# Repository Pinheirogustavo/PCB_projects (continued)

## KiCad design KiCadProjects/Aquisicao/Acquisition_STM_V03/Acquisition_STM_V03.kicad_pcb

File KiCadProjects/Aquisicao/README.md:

# Placa de Aquisição 

## Versão atual em produção (jlcpcb:): 01

## Descrição Geral do projeto
 As placas de aquisição tem a função de suportar os módulos de microcontroladores stm32 modelo bluepill, empregados na demodulação de sinais.

### Versão 01

Esta versão suporta até 4 módulos stm32 bluepill. Onde é possível demodular 4 ou 8 canais externos em cada módulo.

A versão de barramento suportada é:

A alimentação de cada módulo é "dedicada". Isto é, há um regulador de tensão StepDown implementado na placa que fornece a tensão de 5V (5V_stepdown), que é regulada a 3.3V (3,3V_step) que é empregada na alimentação dos módulos. Em resumo os estágios são:

VCC (barramento) &rarr; 5V (StepDown) &rarr; 3V (regulador) &rarr; entrada 3.3V bluepill

As entradas analógicas fixas de cada módulo são:

> PA1 - Amplitude da corrente I1 (Ampl1)

> PA4 - Amplitude da corrente I2 (Ampl2)

As entradas analógicas de cada módulo referentos aos canais externos são:

> PA0 - Canal X (sign_Cx)

> PB0 - Canal X+4 (sign_Cx+4)

>Estes canais externos não estão implementados no barramento, mas sim por conectores de pinos horizontais laterais identificados por "sign_C" (elementos J4 e J5).

As conexões de comunicação de cada módulo são (I2C):

> PB6 - SCL1 (3.3V)

> PB7 - SDA1 (3.3V)

As entradas digitais reservadas para sinais de sincronismo são:

> PA5 - SINC_A

> PA6 - SINC_B

> PA7 - SINC_C

> PB1 - SINCD

Assim, a ideia é que a placa opere em dois modos:

- Modo 1: leitura da amplitude de corrente individualmente em cada microcontrolador.
    Dado que o microcontrolador opera com dois ADCs, um estaria dedicado a ler algum sinal de corrente (I1 ou I2) e o segundo dedicado a ler um dos sinais vindos dos canais externos), possibilitando a leitura de 4 canais por placa de aquisição.

- Modo 2: leitura apenas dos canais externos por cada microcontrolador, sem leitura da corrente.
    Nesse modo os dois ADCs de cada microcontrolador realizam a leitura dos dois canais externos (X) e (X+4), possibilitando a leitura de 8 canais por placa de aquisição.

### Versao 02

### Versão 03

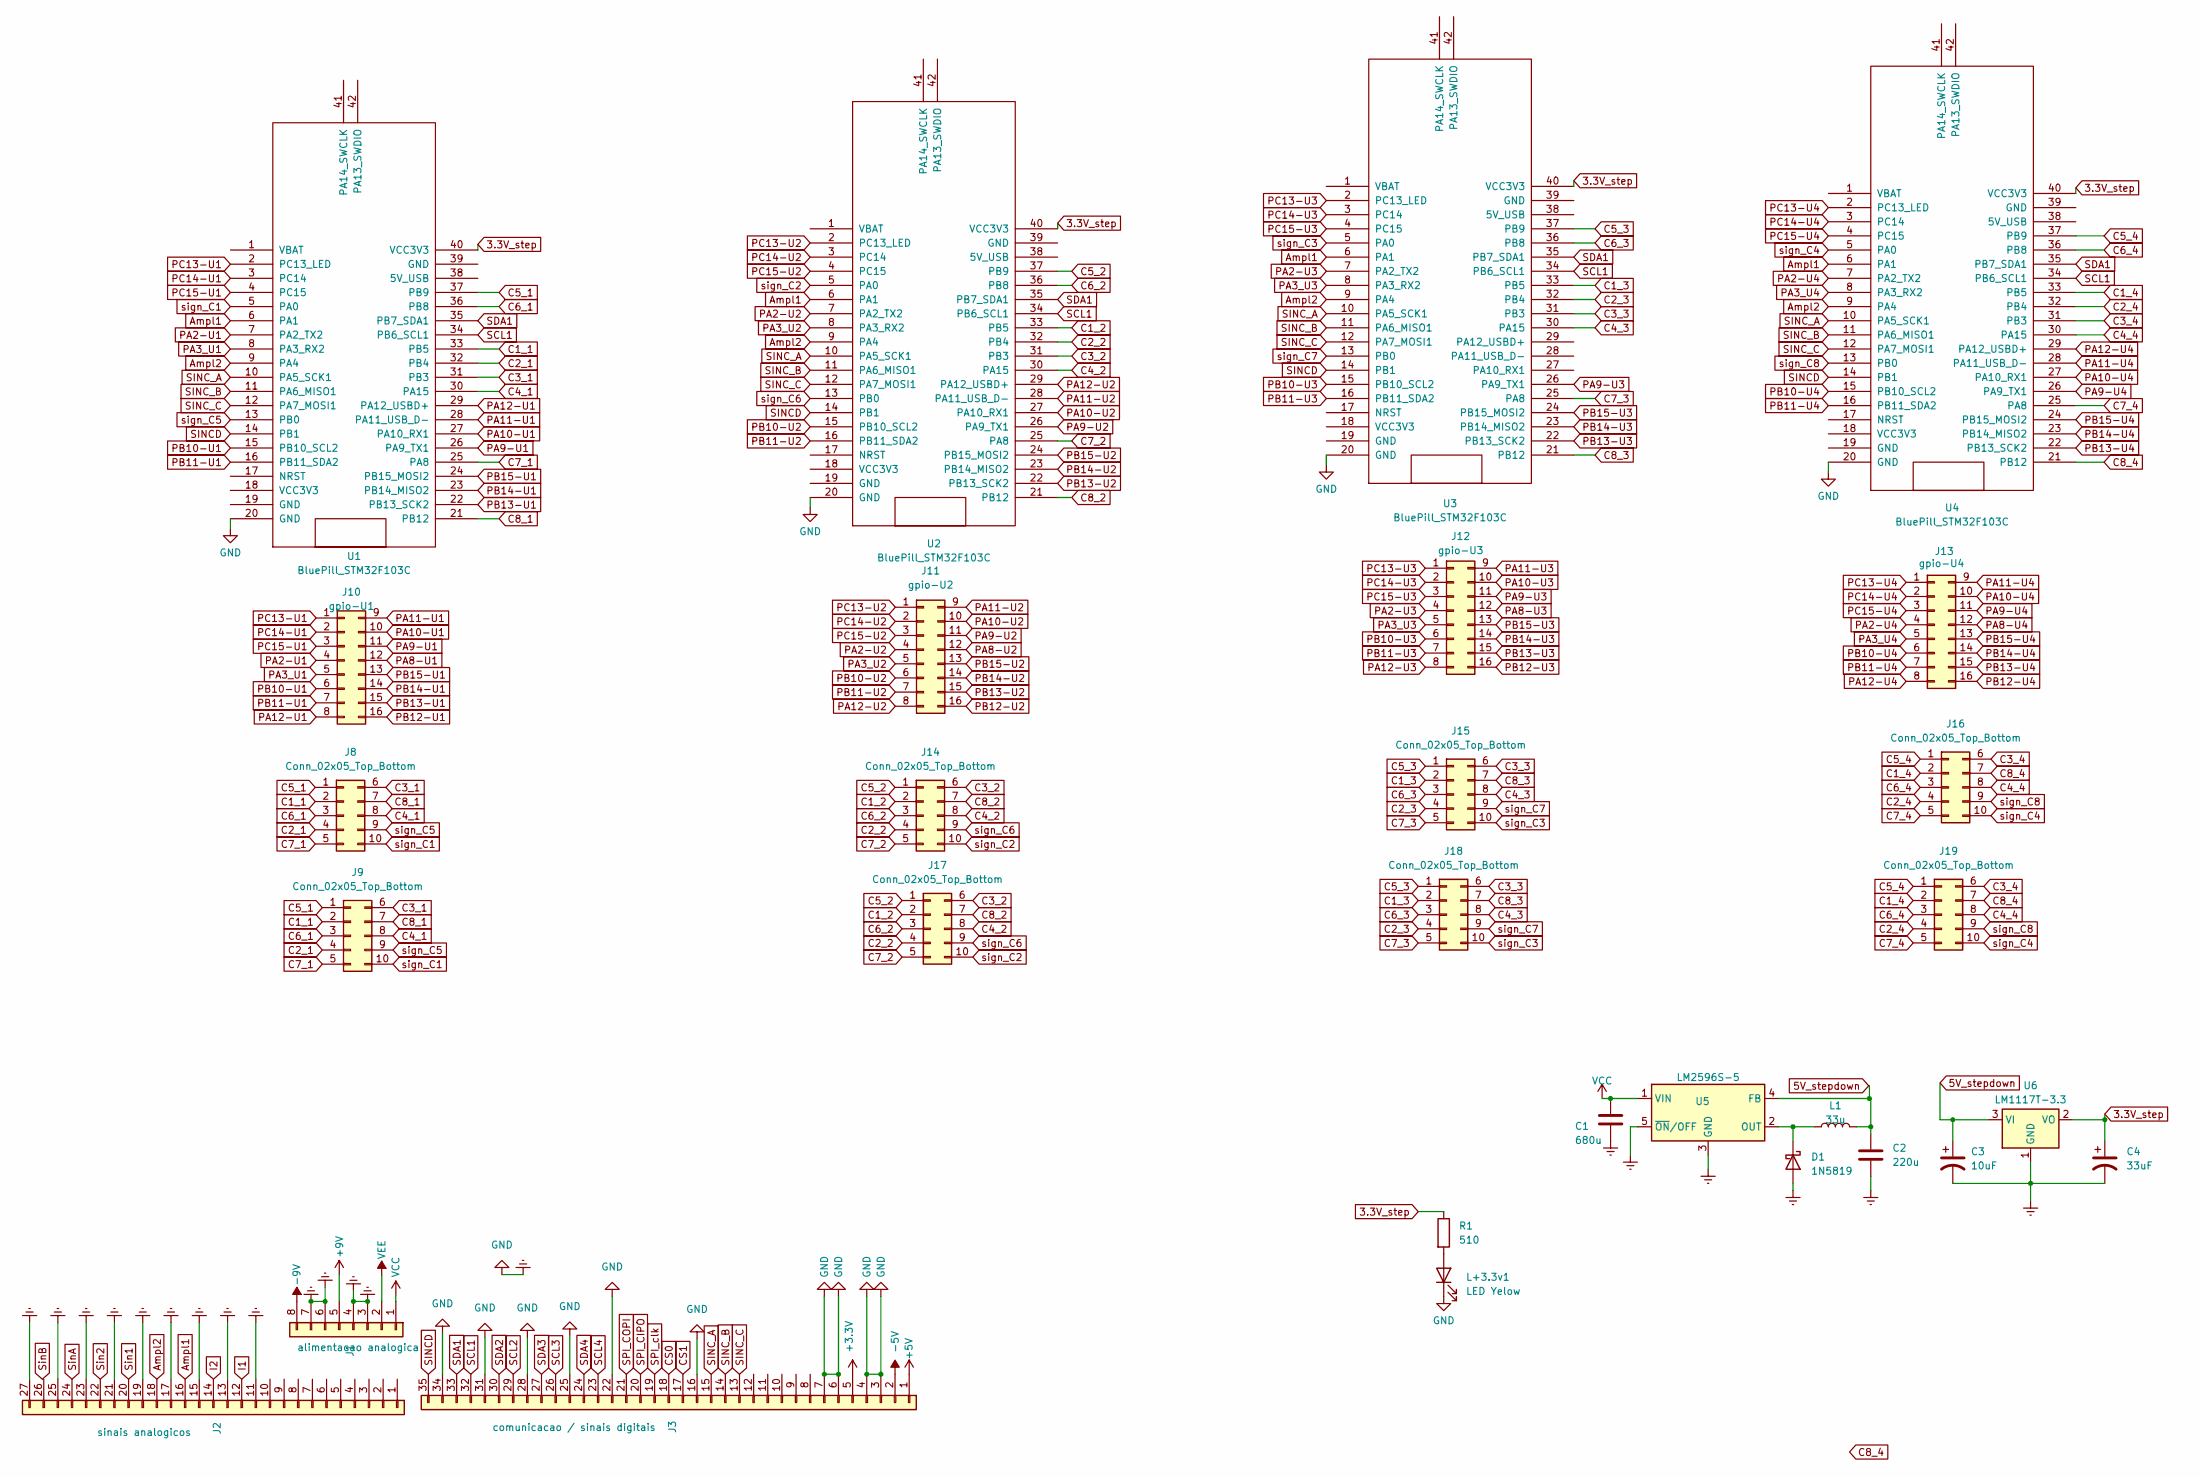
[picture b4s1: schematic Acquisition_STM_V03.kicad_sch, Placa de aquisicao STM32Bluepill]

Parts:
C1: 680u; CP_Radial_D5.0mm_P2.50mm
C2: 220u; CP_Radial_D5.0mm_P2.50mm
C3: 10uF; CP_Radial_Tantal_D4.5mm_P2.50mm
C4: 33uF; CP_Radial_Tantal_D4.5mm_P2.50mm
D1: 1N5819; D_DO-41_SOD81_P10.16mm_Horizontal
J1: alimentacao analogica; PinHeader_1x08_P2.54mm_Vertical
J2: sinais analogicos; PinHeader_1x27_P2.54mm_Vertical
J3: comunicacao / sinais digitais; PinHeader_1x35_P2.54mm_Vertical
J8, J9, J14, J15, J16, J17, J18, J19: Conn_02x05_Top_Bottom; PinHeader_2x05_P2.54mm_Horizontal
J10: gpio-U1; PinHeader_2x08_P2.54mm_Vertical
J11: gpio-U2; PinHeader_2x08_P2.54mm_Vertical
J12: gpio-U3; PinHeader_2x08_P2.54mm_Vertical
J13: gpio-U4; PinHeader_2x08_P2.54mm_Vertical
L1: 33u; L_7.3x7.3_H4.5
L+3.3v1: LED Yelow; LED_D5.0mm
R1: 510; R_Axial_DIN0207_L6.3mm_D2.5mm_P7.62mm_Horizontal
U1, U2, U3, U4: BluePill_STM32F103C
U5: LM2596S-5; TO-220-5_P3.4x3.7mm_StaggerOdd_Lead3.8mm_Vertical
U6: LM1117T-3.3; TO-220-3_Vertical

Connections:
3.3V_step: C4.1, R1.1, U1.40 (VCC3V3), U2.40 (VCC3V3), U3.40 (VCC3V3), U4.40 (VCC3V3), U6.2 (VO)
5V_stepdown: C2.1, C3.1, L1.2, U5.4 (FB), U6.3 (VI)
+3.3V: J3.5
+5V: J3.1
+9V: J1.5
-5V: J3.2
-9V: J1.8
Ampl1: J2.16, U1.6 (PA1), U2.6 (PA1), U3.6 (PA1), U4.6 (PA1)
Ampl2: J2.18, U1.9 (PA4), U2.9 (PA4), U3.9 (PA4), U4.9 (PA4)
C1_1: J8.2, J9.2, U1.33 (PB5)
C1_2: J14.2, J17.2, U2.33 (PB5)
C1_3: J15.2, J18.2, U3.33 (PB5)
C1_4: J16.2, J19.2, U4.33 (PB5)
C2_1: J8.4, J9.4, U1.32 (PB4)
C2_2: J14.4, J17.4, U2.32 (PB4)
C2_3: J15.4, J18.4, U3.32 (PB4)
C2_4: J16.4, J19.4, U4.32 (PB4)
C3_1: J8.6, J9.6, U1.31 (PB3)
C3_2: J14.6, J17.6, U2.31 (PB3)
C3_3: J15.6, J18.6, U3.31 (PB3)
C3_4: J16.6, J19.6, U4.31 (PB3)
C4_1: J8.8, J9.8, U1.30 (PA15)
C4_2: J14.8, J17.8, U2.30 (PA15)
C4_3: J15.8, J18.8, U3.30 (PA15)
C4_4: J16.8, J19.8, U4.30 (PA15)
C5_1: J8.1, J9.1, U1.37 (PB9)
C5_2: J14.1, J17.1, U2.37 (PB9)
C5_3: J15.1, J18.1, U3.37 (PB9)
C5_4: J16.1, J19.1, U4.37 (PB9)
C6_1: J8.3, J9.3, U1.36 (PB8)
C6_2: J14.3, J17.3, U2.36 (PB8)
C6_3: J15.3, J18.3, U3.36 (PB8)
C6_4: J16.3, J19.3, U4.36 (PB8)
C7_1: J8.5, J9.5, U1.25 (PA8)
C7_2: J14.5, J17.5, U2.25 (PA8)
C7_3: J15.5, J18.5, U3.25 (PA8)
C7_4: J16.5, J19.5, U4.25 (PA8)
C8_1: J8.7, J9.7, U1.21 (PB12)
C8_2: J14.7, J17.7, U2.21 (PB12)
C8_3: J15.7, J18.7, U3.21 (PB12)
C8_4: J16.7, J19.7, U4.21 (PB12)
CS0: J3.18
CS1: J3.17
Earth: C1.2, C2.2, C3.2, C4.2, D1.2 (A), J1.3, J1.4, J1.6, J1.7, J2.11, J2.13, J2.15, J2.17, J2.19, J2.21, J2.23, J2.25, J2.27, J3.3, J3.4, J3.6, J3.7, J3.16, J3.22, J3.25, J3.28, J3.31, J3.34, L+3.3v1.1 (K), U1.20 (GND), U2.20 (GND), U3.20 (GND), U4.20 (GND), U5.3 (GND), U5.5 (~ON/OFF), U6.1 (GND)
I1: J2.12
I2: J2.14
unnamed: D1.1 (K), L1.1, U5.2 (OUT)
unnamed: L+3.3v1.2 (A), R1.2
PA2-U1: J10.4, U1.7 (PA2_TX2)
PA2-U2: J11.4, U2.7 (PA2_TX2)
PA2-U3: J12.4, U3.7 (PA2_TX2)
PA2-U4: J13.4, U4.7 (PA2_TX2)
PA3_U1: J10.5, U1.8 (PA3_RX2)
PA3_U2: J11.5, U2.8 (PA3_RX2)
PA3_U3: J12.5, U3.8 (PA3_RX2)
PA3_U4: J13.5, U4.8 (PA3_RX2)
PA8-U1: J10.12
PA8-U2: J11.12
PA8-U3: J12.12
PA8-U4: J13.12
PA9-U1: J10.11, U1.26 (PA9_TX1)
PA9-U2: J11.11, U2.26 (PA9_TX1)
PA9-U3: J12.11, U3.26 (PA9_TX1)
PA9-U4: J13.11, U4.26 (PA9_TX1)
PA10-U1: J10.10, U1.27 (PA10_RX1)
PA10-U2: J11.10, U2.27 (PA10_RX1)
PA10-U3: J12.10
PA10-U4: J13.10, U4.27 (PA10_RX1)
PA11-U1: J10.9, U1.28 (PA11_USB_D-)
PA11-U2: J11.9, U2.28 (PA11_USB_D-)
PA11-U3: J12.9
PA11-U4: J13.9, U4.28 (PA11_USB_D-)
PA12-U1: J10.8, U1.29 (PA12_USBD+)
PA12-U2: J11.8, U2.29 (PA12_USBD+)
PA12-U3: J12.8
PA12-U4: J13.8, U4.29 (PA12_USBD+)
PB10-U1: J10.6, U1.15 (PB10_SCL2)
PB10-U2: J11.6, U2.15 (PB10_SCL2)
PB10-U3: J12.6, U3.15 (PB10_SCL2)
PB10-U4: J13.6, U4.15 (PB10_SCL2)
PB11-U1: J10.7, U1.16 (PB11_SDA2)
PB11-U2: J11.7, U2.16 (PB11_SDA2)
PB11-U3: J12.7, U3.16 (PB11_SDA2)
PB11-U4: J13.7, U4.16 (PB11_SDA2)
PB12-U1: J10.16
PB12-U2: J11.16
PB12-U3: J12.16
PB12-U4: J13.16
PB13-U1: J10.15, U1.22 (PB13_SCK2)
PB13-U2: J11.15, U2.22 (PB13_SCK2)
PB13-U3: J12.15, U3.22 (PB13_SCK2)
PB13-U4: J13.15, U4.22 (PB13_SCK2)
PB14-U1: J10.14, U1.23 (PB14_MISO2)
PB14-U2: J11.14, U2.23 (PB14_MISO2)
PB14-U3: J12.14, U3.23 (PB14_MISO2)
PB14-U4: J13.14, U4.23 (PB14_MISO2)
PB15-U1: J10.13, U1.24 (PB15_MOSI2)
PB15-U2: J11.13, U2.24 (PB15_MOSI2)
PB15-U3: J12.13, U3.24 (PB15_MOSI2)
PB15-U4: J13.13, U4.24 (PB15_MOSI2)
PC13-U1: J10.1, U1.2 (PC13_LED)
PC13-U2: J11.1, U2.2 (PC13_LED)
PC13-U3: J12.1, U3.2 (PC13_LED)
PC13-U4: J13.1, U4.2 (PC13_LED)
PC14-U1: J10.2, U1.3 (PC14)
PC14-U2: J11.2, U2.3 (PC14)
PC14-U3: J12.2, U3.3 (PC14)
PC14-U4: J13.2, U4.3 (PC14)
PC15-U1: J10.3, U1.4 (PC15)
PC15-U2: J11.3, U2.4 (PC15)
PC15-U3: J12.3, U3.4 (PC15)
PC15-U4: J13.3, U4.4 (PC15)
SCL1: J3.32, U1.34 (PB6_SCL1), U2.34 (PB6_SCL1), U3.34 (PB6_SCL1), U4.34 (PB6_SCL1)
SCL2: J3.29
SCL3: J3.26
SCL4: J3.23
SDA1: J3.33, U1.35 (PB7_SDA1), U2.35 (PB7_SDA1), U3.35 (PB7_SDA1), U4.35 (PB7_SDA1)
SDA2: J3.30
SDA3: J3.27
SDA4: J3.24
SINCD: J3.35, U1.14 (PB1), U2.14 (PB1), U3.14 (PB1), U4.14 (PB1)
SINC_A: J3.15, U1.10 (PA5_SCK1), U2.10 (PA5_SCK1), U3.10 (PA5_SCK1), U4.10 (PA5_SCK1)
SINC_B: J3.14, U1.11 (PA6_MISO1), U2.11 (PA6_MISO1), U3.11 (PA6_MISO1), U4.11 (PA6_MISO1)
SINC_C: J3.13, U1.12 (PA7_MOSI1), U2.12 (PA7_MOSI1), U3.12 (PA7_MOSI1), U4.12 (PA7_MOSI1)
SPI_CIPO: J3.20
SPI_COPI: J3.21
SPI_clk: J3.19
Sin1: J2.20
Sin2: J2.22
SinA: J2.24
SinB: J2.26
VCC: C1.1, J1.1, U5.1 (VIN)
VEE: J1.2
sign_C1: J8.10, J9.10, U1.5 (PA0)
sign_C2: J14.10, J17.10, U2.5 (PA0)
sign_C3: J15.10, J18.10, U3.5 (PA0)
sign_C4: J16.10, J19.10, U4.5 (PA0)
sign_C5: J8.9, J9.9, U1.13 (PB0)
sign_C6: J14.9, J17.9, U2.13 (PB0)
sign_C7: J15.9, J18.9, U3.13 (PB0)
sign_C8: J16.9, J19.9, U4.13 (PB0)

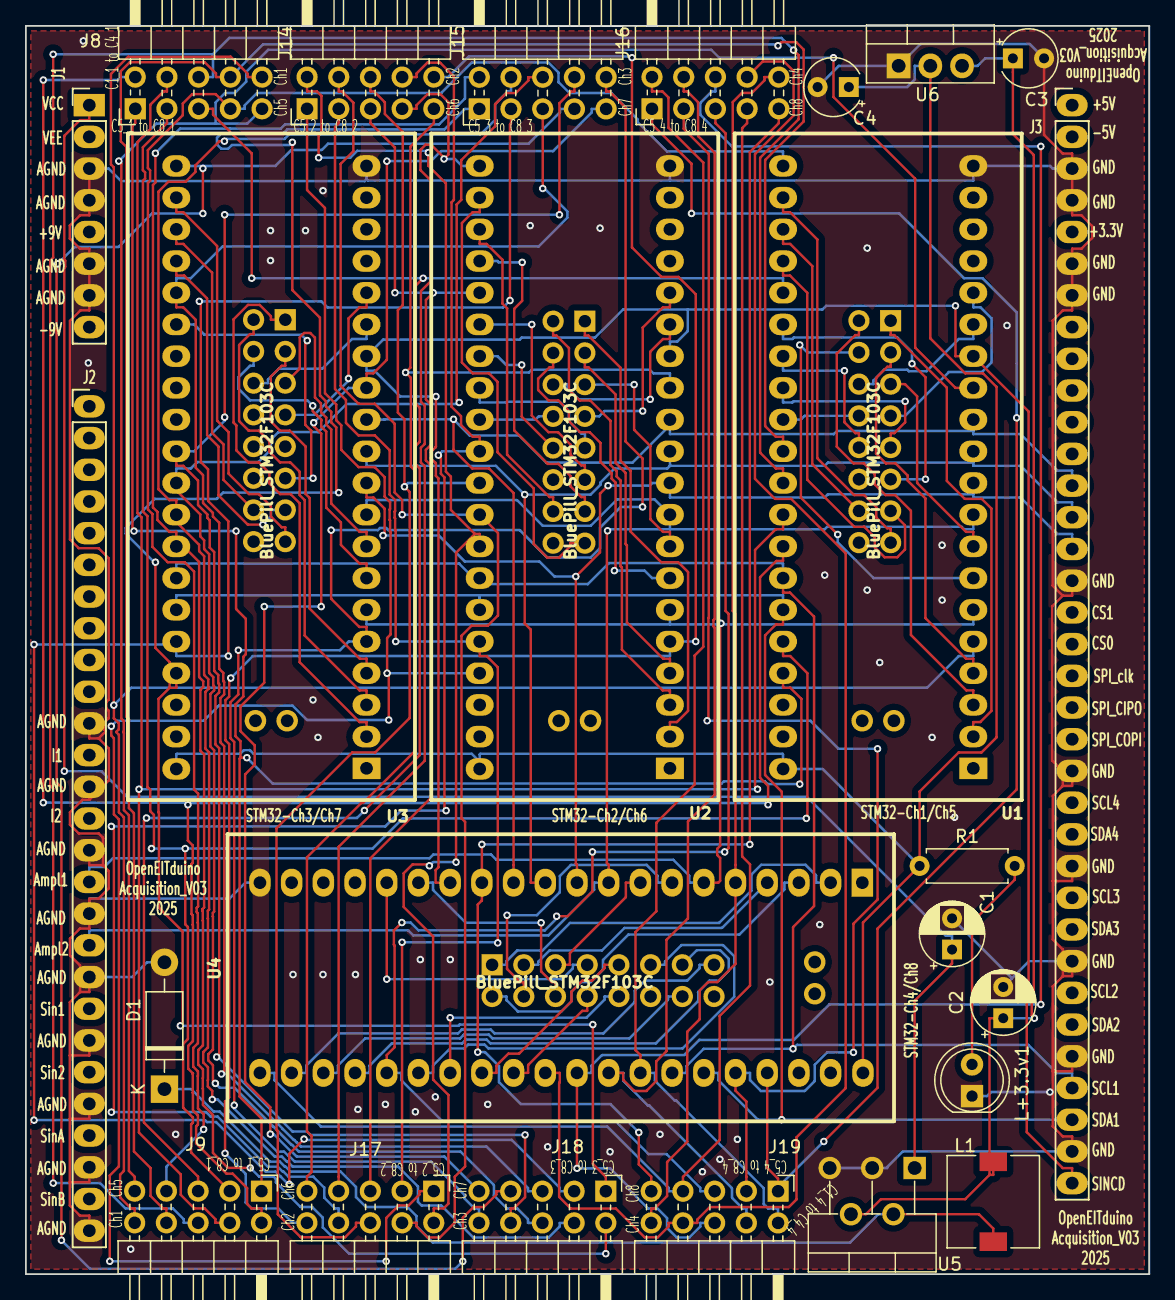
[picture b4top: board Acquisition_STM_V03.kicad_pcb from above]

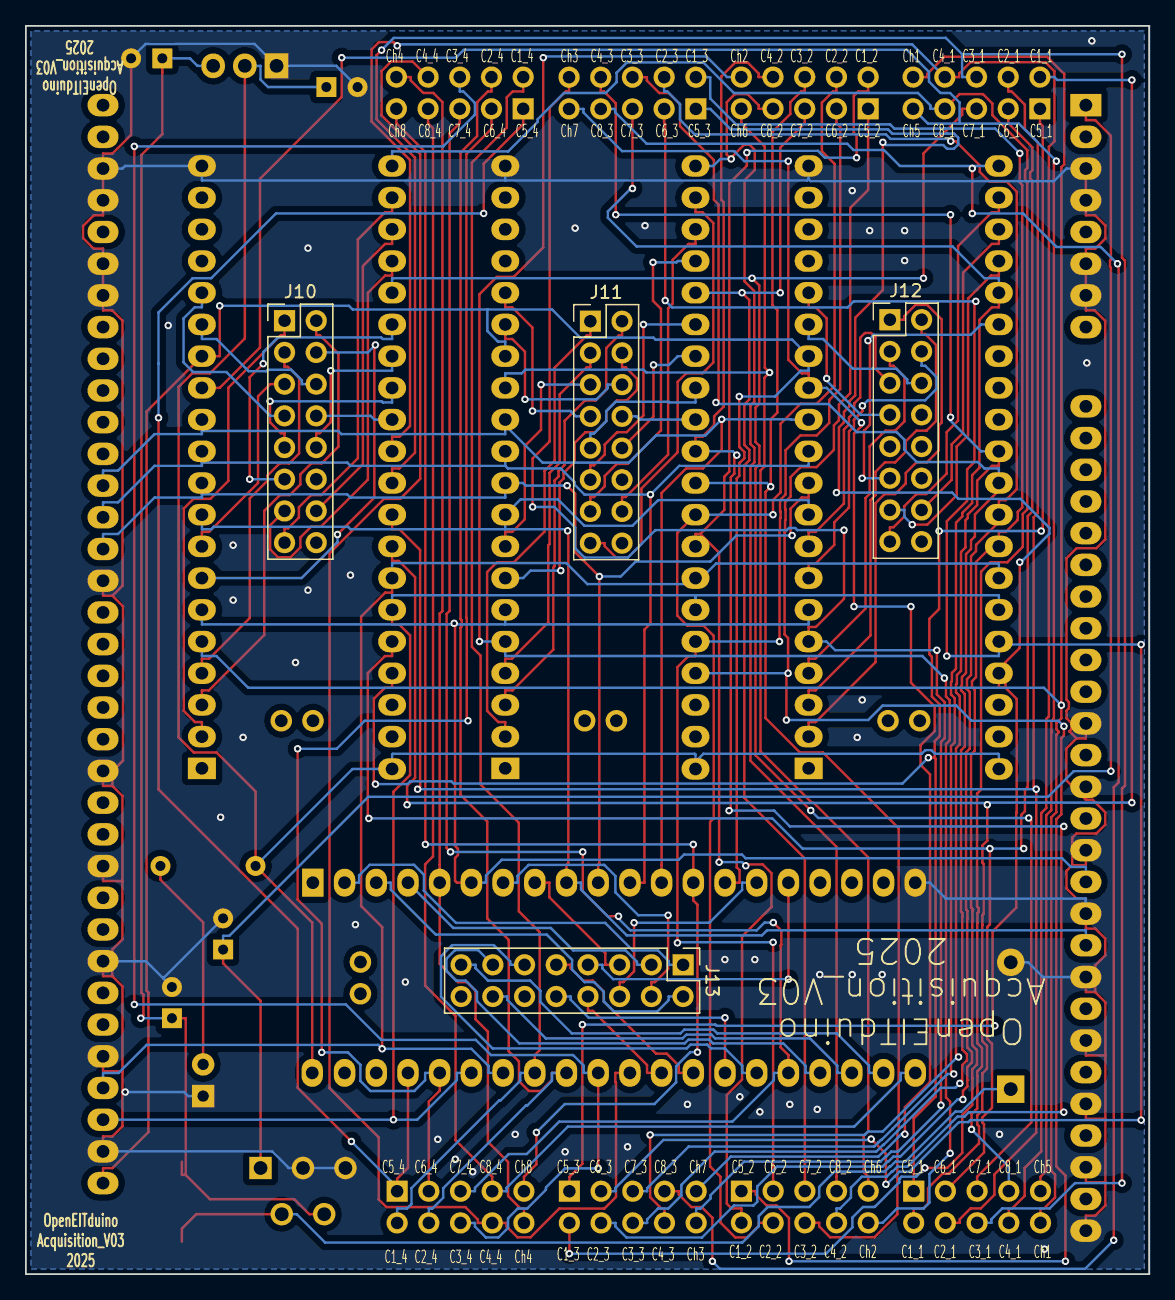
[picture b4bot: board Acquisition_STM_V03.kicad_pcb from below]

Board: 2 copper layers, 90.0 x 100.0 mm, 29 parts (4 on the bottom side), 107 nets.

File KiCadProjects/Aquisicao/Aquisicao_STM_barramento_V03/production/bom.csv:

Designator,Footprint,Quantity,Value,LCSC Part #
C1,CP_Radial_D5.0mm_P2.50mm,1,680u,
C2,CP_Radial_D5.0mm_P2.50mm,1,220u,
C3,CP_Radial_Tantal_D4.5mm_P2.50mm,1,10uF,
C4,CP_Radial_Tantal_D4.5mm_P2.50mm,1,33uF,
D1,D_DO-41_SOD81_P10.16mm_Horizontal,1,1N5819,
J1,PinHeader_1x08_P2.54mm_Vertical,1,alimentacao analogica,
J10,PinHeader_2x08_P2.54mm_Vertical,1,gpio-U1,
J11,PinHeader_2x08_P2.54mm_Vertical,1,gpio-U2,
J12,PinHeader_2x08_P2.54mm_Vertical,1,gpio-U3,
J13,PinHeader_2x08_P2.54mm_Vertical,1,gpio-U4,
"J14, J15, J16, J17, J18, J19, J8, J9",PinHeader_2x05_P2.54mm_Horizontal,8,Conn_02x05_Top_Bottom,
J2,PinHeader_1x27_P2.54mm_Vertical,1,sinais analogicos,
J3,PinHeader_1x35_P2.54mm_Vertical,1,comunicacao / sinais digitais,
L+3.3V1,LED_D5.0mm,1,LED Yelow,
L1,L_7.3x7.3_H4.5,1,33u,
R1,R_Axial_DIN0207_L6.3mm_D2.5mm_P7.62mm_Horizontal,1,510,
"U1, U2, U3, U4",BluePill_STM32F103C,4,BluePill_STM32F103C,
U5,TO-220-5_P3.4x3.7mm_StaggerOdd_Lead3.8mm_Vertical,1,LM2596S-5,
U6,TO-220-3_Vertical,1,LM1117T-3.3,

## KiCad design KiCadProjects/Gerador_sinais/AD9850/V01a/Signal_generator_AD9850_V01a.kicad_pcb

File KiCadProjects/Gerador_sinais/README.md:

# Gerador de Sinais

## Descrição Geral do projeto

Sistema que gera um sinal senoidal com controle de amplitude e frequência.

Estágios: Gerador de sinais ( CA@300mV + DC) &rarr; Filtro  passa-alta &rarr; SinA (CA@300mV) &rarr; buffer &rarr;  amplificador não-inversor &rarr; Sin1(CA@300mV-3V).

## Componentes do circuito:

- Arduino nano: controlador do sistema
- AD9833: gerador de sinais confeccionado em módulo. Gera uma onda senoidal de amplitude fixa de 300mA e offset
- Ad828: Amplificador operacional dedicado ao ganho de sinal. 
	>Amplificador 1 é buffer entre o filtro passa-alta e o circuito de ganho.
	>Amplificador 2 é um amplificador não inversor. Vout = (1+pot/R2)*Vin
- X9c10x: potenciometro digital dedicado ao ganho de sinal

##Cuidados a serem tomados

Para a comunicação SPI, o dispositivo a ser controlado (Chip Select) é selecionado quando o respectivo pino CS está em LOW. Nunca pode-se permitir que dois dispositivos estejam com CS em LOW ao mesmo tempo. Por isso, no programa é preciso garantir que as operações com o AD9833 (select_wave, freq+ e freq-)  após um delay tragam o sinal do CS(AD9833) para LOW e depois devolvam para HIGH. E que as operações com o X9110X (aumento de R, redução de R, guardar R) após um delay tragam o sinal do CS(X9c10X) para LOW e depois devolvam para HIGH.

Assim, primeiramente o programa deve liberar o AD9833 (gerador de sinais) para ocupar a comunicação SPI, após a geração de sinal, desligar sua comunicação (trazer seu CS para HIGH) e liberar a comunicação SPI para ser requisitada a partir dos botões referentes a cada dispositivo. 

## Estágios do circuito

#### Entradas e saídas digitais do arduino nano:

>D2:  cs (X9X104) - Saída digital. Sinal de Chip Select do potenciômetro digital - "The device is selected when the CS input is LOW." 

>D3: storage_R - Usado para armazenar o valor de resistência - Botão 4 - Pressionar o botão faz o sinal X9c10x_INC  ficar em HIGH e o sinal  cs(X9X104) passar de HIGH para LOW e retornar a HIGH

>D4:  cs (AD9833) - Sinal de Chip Select do gerador de sinais

>D5:  Up_pot - Aumenta a resistência do potenciômetro (aumenta o ganho do sistema) - Botão 5 - Pressionar o botão faz com que o sinal de cs(X9X104) passe de HIGH para LOW, que o sinal X9c10x_INC altere de HIGH para LOW e o sinal  X9c10x_U/D fique em HIGH. Ao liberar o botão, o sinal de cs(X9X104) deve retornar para HIGH.
	 
>D6:  Down_pot - Reduz a resistência do potenciômetro (reduz o ganho do sistema) - Botão 6 - Pressionar o botão faz com que o sinal de cs(X9X104) passe de HIGH para LOW, X9c10x_INC altere de HIGH para LOW e o sinal  X9c10x_U/D fique em LOW. Ao liberar o botão, o sinal de cs(X9X104) deve retornar para HIGH.

>D7:  X9c10x_INC - Saída digital. Responsável pelo disparo do sinal que habilita o incremento e o decremento da resistência. Alterado pelos sinais em Up_pot/Down_pot.

>D8:  X9c10x_U/D -  Saída digital. Responsável pela seleção do sinal de incremento ou decremento da resistência. Controlado pelos sinais em Up_pot/Down_pot.

>D9:  freq+   - Incrementa a frequência do sinal (a definir o tamanho do incremento) - Botão 2 - Ainda não implementado no programa.

>D10: freq-   - Decrementa a frequência do sinal (a definir o tamanho do decremento) - Botão 3 - Ainda não implementado no programa.

>D11: SPI_COPI - Saída digital. Sinal de controle do arduino para a entrada SDATA do gerador de sinais.

>D12: S_wave - Seleciona a forma de onda desejada (seno, triangular ou quadrada) - Botão 1 - Ainda não implementado no programa.

>D13: SPI_clk - Saída digital. Sinal de clock entre o arduino e o gerador de sinais

#### O potenciômetro digital

- Programa baseado em: https://www.electroniclinic.com/digital-potentiometer-x9c103s-arduino-circuit-and-programming/

- Pin Descriptions - X9c10x:

#### O Gerador de sinais

- Programa baseado em: https://www.electroniclinic.com/ad9833-programmable-waveform-generator-using-arduino/
- Biblioteca necessária: https://github.com/Billwilliams1952/AD9833-Library-Arduino

## Esquemático

## PCB

## PCB-3D

## PCB Máscara

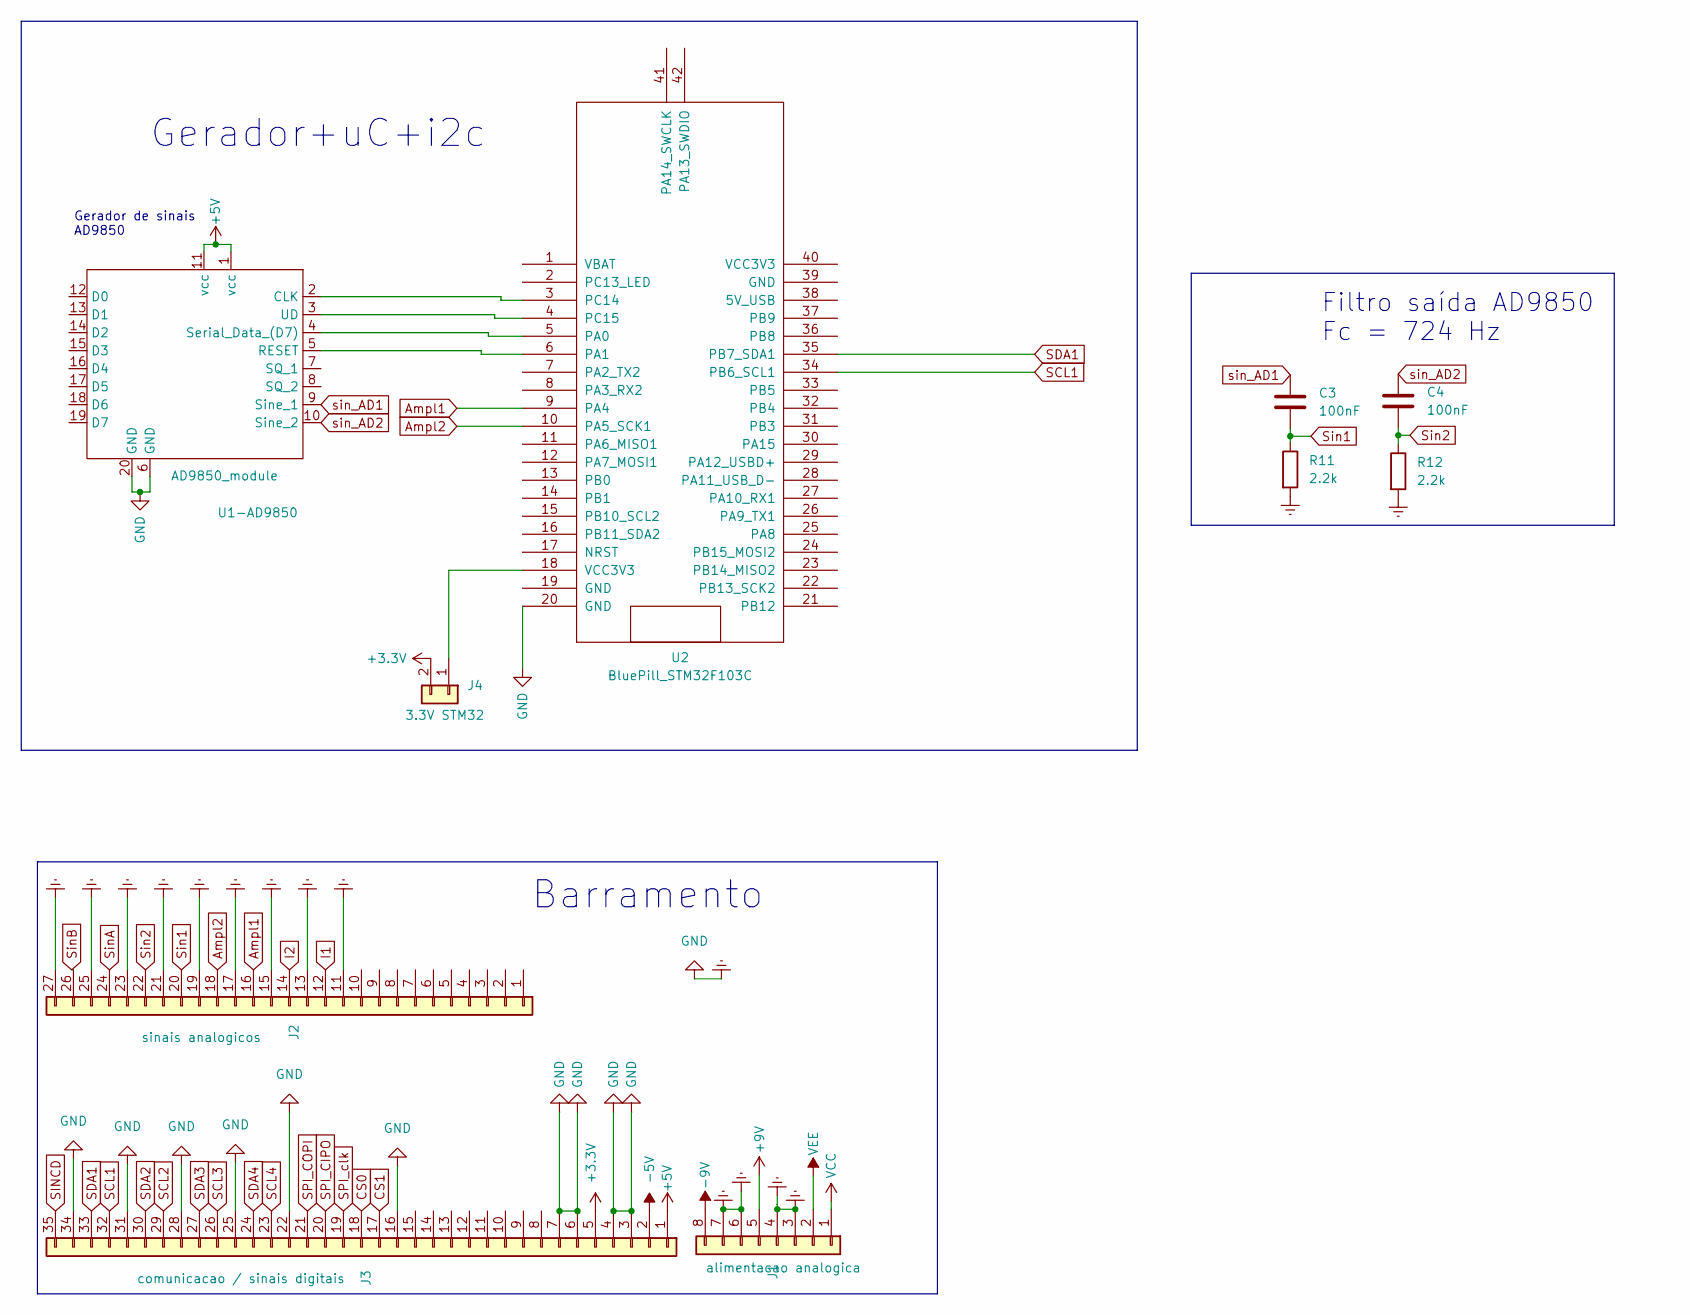
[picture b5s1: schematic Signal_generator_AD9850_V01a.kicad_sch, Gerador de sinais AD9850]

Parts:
C3, C4: 100nF; C_Disc_D3.0mm_W1.6mm_P2.50mm
J1: alimentacao analogica; PinHeader_1x08_P2.54mm_Vertical
J2: sinais analogicos; PinHeader_1x27_P2.54mm_Vertical
J3: comunicacao / sinais digitais; PinHeader_1x35_P2.54mm_Vertical
J4: 3.3V STM32; PinHeader_1x02_P2.54mm_Vertical
R11, R12: 2.2k; R_Axial_DIN0207_L6.3mm_D2.5mm_P7.62mm_Horizontal
U1-AD9850: AD9850_module
U2: BluePill_STM32F103C

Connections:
+3.3V: J3.5, J4.2
+5V: J3.1, U1-AD9850.1 (vcc), U1-AD9850.11 (vcc)
+9V: J1.5
-5V: J3.2
-9V: J1.8
Ampl1: J2.16, U2.9 (PA4)
Ampl2: J2.18, U2.10 (PA5_SCK1)
CS0: J3.18
CS1: J3.17
Earth: J1.3, J1.4, J1.6, J1.7, J2.11, J2.13, J2.15, J2.17, J2.19, J2.21, J2.23, J2.25, J2.27, J3.3, J3.4, J3.6, J3.7, J3.16, J3.22, J3.25, J3.28, J3.31, J3.34, R11.2, R12.2, U1-AD9850.6 (GND), U1-AD9850.20 (GND), U2.20 (GND)
I1: J2.12
I2: J2.14
unnamed: J4.1, U2.18 (VCC3V3)
unnamed: U1-AD9850.2 (CLK), U2.3 (PC14)
unnamed: U1-AD9850.5 (RESET), U2.6 (PA1)
unnamed: U1-AD9850.4 (Serial_Data_(D7)), U2.5 (PA0)
unnamed: U1-AD9850.3 (UD), U2.4 (PC15)
SCL1: J3.32, U2.34 (PB6_SCL1)
SCL2: J3.29
SCL3: J3.26
SCL4: J3.23
SDA1: J3.33, U2.35 (PB7_SDA1)
SDA2: J3.30
SDA3: J3.27
SDA4: J3.24
SINCD: J3.35
SPI_CIPO: J3.20
SPI_COPI: J3.21
SPI_clk: J3.19
Sin1: C3.2, J2.20, R11.1
Sin2: C4.2, J2.22, R12.1
SinA: J2.24
SinB: J2.26
VCC: J1.1
VEE: J1.2
sin_AD1: C3.1, U1-AD9850.9 (Sine_1)
sin_AD2: C4.1, U1-AD9850.10 (Sine_2)

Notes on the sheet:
Gerador+uC+i2c
Filtro saída AD9850 Fc = 724 Hz
Gerador de sinais AD9850
Barramento

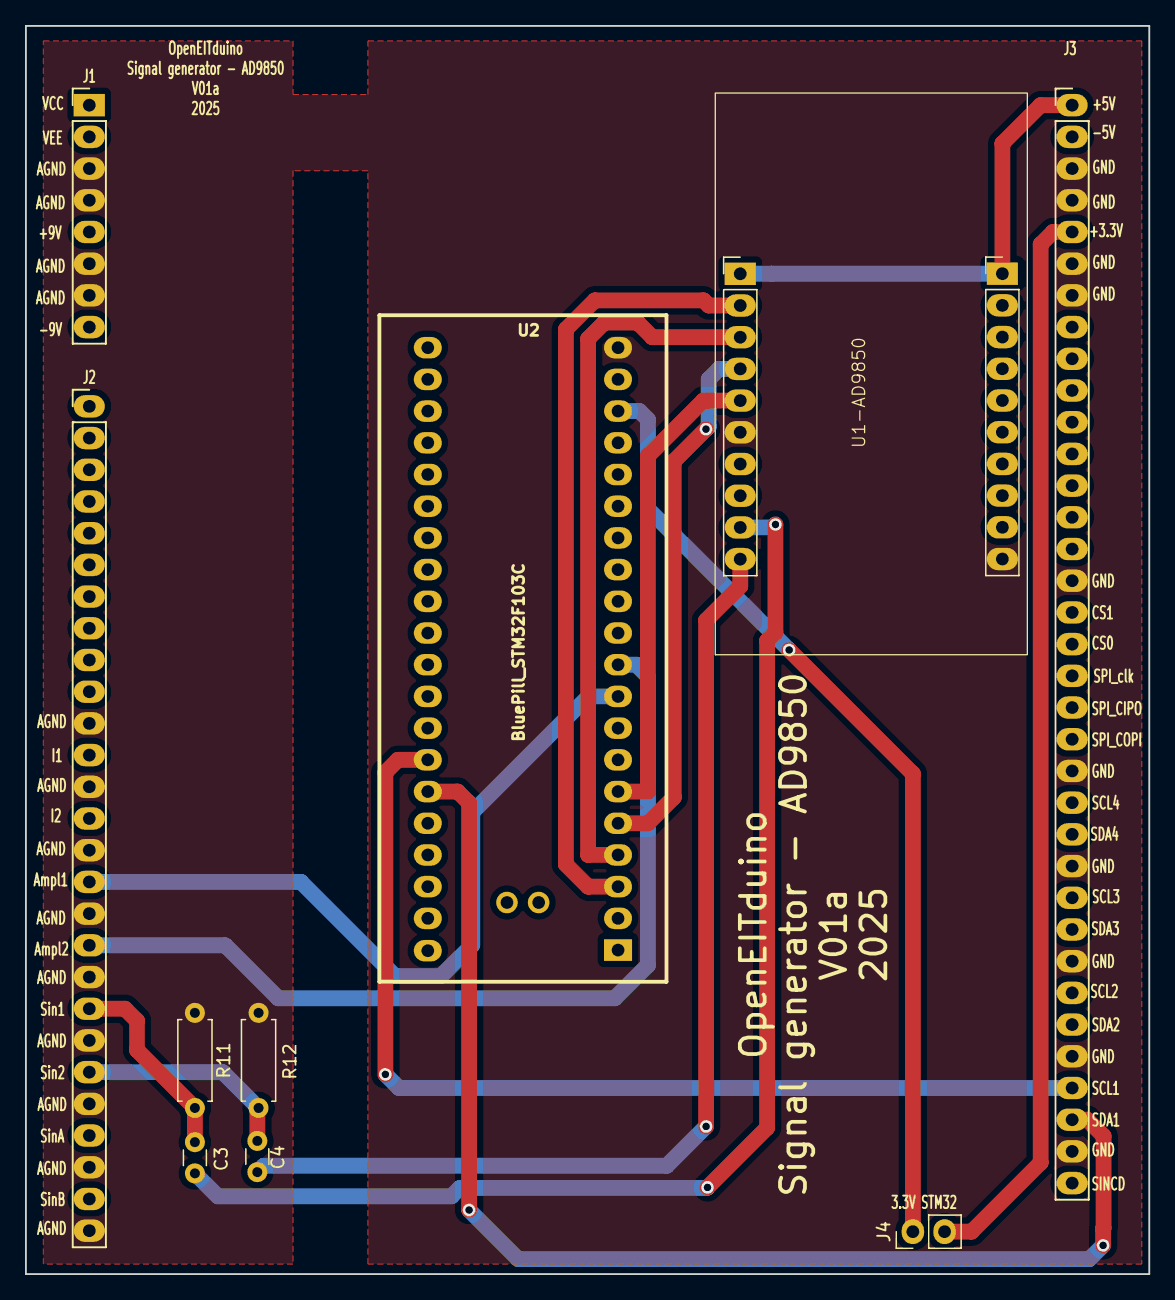
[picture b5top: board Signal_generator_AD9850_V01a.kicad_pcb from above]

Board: 2 copper layers, 90.0 x 100.0 mm, 10 parts (0 on the bottom side), 16 nets.
